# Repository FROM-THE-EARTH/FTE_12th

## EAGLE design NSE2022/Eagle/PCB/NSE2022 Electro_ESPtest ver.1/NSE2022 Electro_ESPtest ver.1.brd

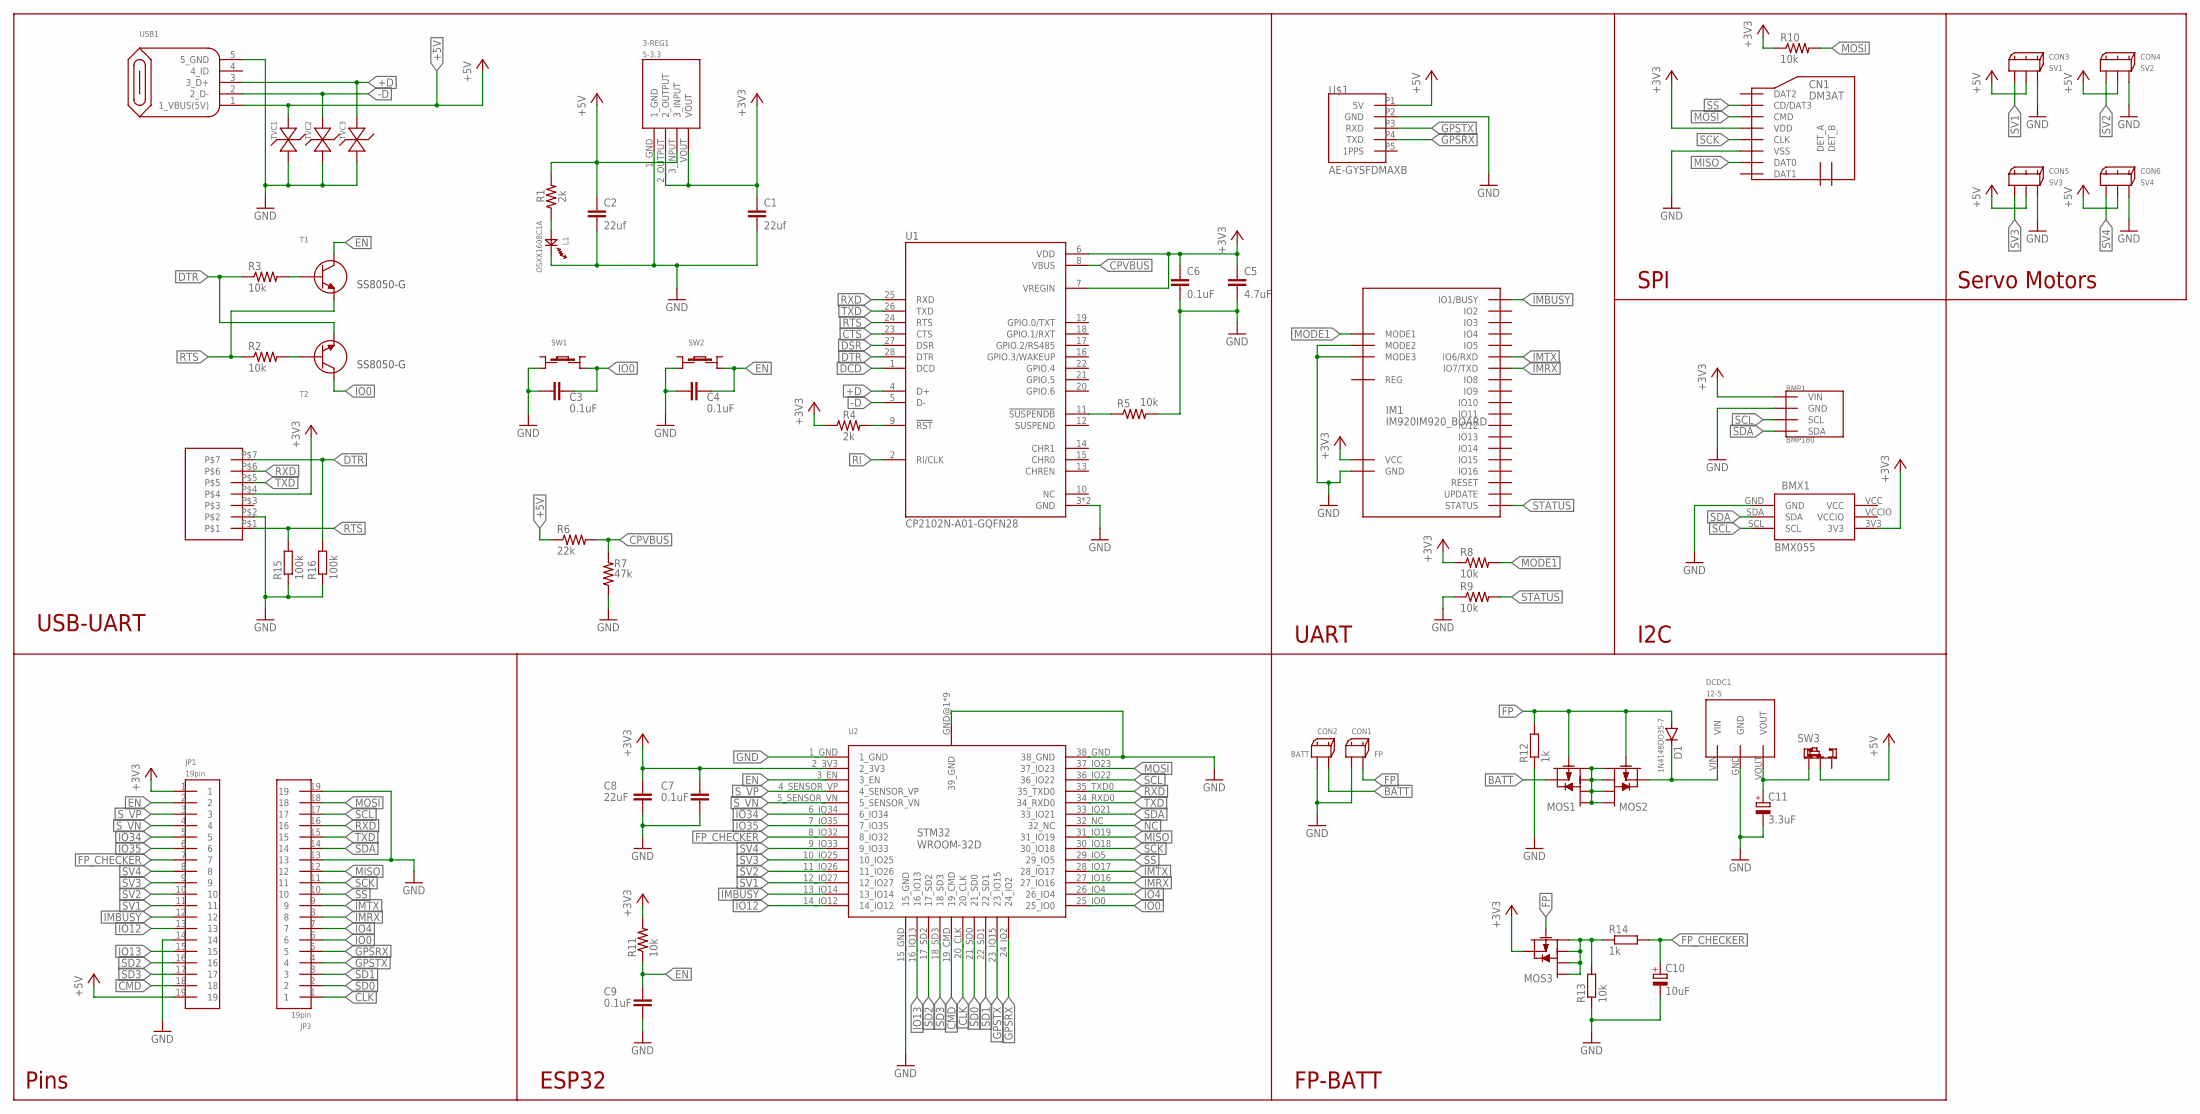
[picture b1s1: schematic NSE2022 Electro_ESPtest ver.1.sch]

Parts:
3-REG1: 5-3.3; AZ1117CH-3.3TRG1
BMP1: BMP180; GY-68
BMX1: BMX055
C1, C2: 22uf; C0603
C3, C4, C6, C7, C9: 0.1uF; C0603
C5: 4.7uF; C0402
C8: 22uF; C0603
C10: 10uF; E2,5-5
C11: 3.3uF; E2,5-5
CN1: DM3AT
CON1: FP; 2.5_MINI-SPOX_2PIN
CON2: BATT; 2.5_MINI-SPOX_2PIN
CON3: SV1; 2.5_MINI-SPOX_3PIN
CON4: SV2; 2.5_MINI-SPOX_3PIN
CON5: SV3; 2.5_MINI-SPOX_3PIN
CON6: SV4; 2.5_MINI-SPOX_3PIN
D1: 1N4148DO35-7; DO35-7
DCDC1: 12-5; 5V1A_M78AR05-1
IM1: IM920IM920_BOARD; IM920_BOARD
JP1, JP3: 19pin; 19_2.54
JP2: 7pin; 7_2.54
L1: OSXX1608C1A
MOS1, MOS2, MOS3: PCH_SSM6J808R; SSM6J808R
R1, R4: 2k; R0201
R2, R3, R5, R8, R9, R10, R11: 10k; R0201
R6: 22k; R0201
R7: 47k; R0201
R12, R14: 1k; 0207/10
R13: 10k; 0207/10
R15, R16: 100k; 0207/10
SW1, SW2: TS-06104
SW3: SRIDE_SWITCH
T1, T2: NPN_SS8050-G
TVC1, TVC2, TVC3: ESD5484FCT5G
U1: CP2102N-A01-GQFN28; QFN50P500X500X80-29N
U2: ESP32-WROOM-32D
U$1: AE-GYSFDMAXB
USB1: MICRO-B_ZX62R-B-5P

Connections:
+3V3: 3-REG1.2_OUTPUT, 3-REG1.VOUT, BMP1.P1 (VIN), BMX1.3V3, C1.1, C5.1, C6.1, C7.1, C8.1, CN1.VDD, IM1.IO23 (VCC), JP1.1, JP2.P$4, MOS3.S, R4.1, R8.1, R10.1, R11.2, U1.6 (VDD), U1.7 (VREGIN), U2.2_3V3
+5V: 3-REG1.3_INPUT, C2.1, CON3.2, CON4.2, CON5.2, CON6.2, JP1.19, R1.2, R6.1, SW3.LR, TVC1.2_AN, U$1.P1 (5V), USB1.1 (1_VBUS(5V))
+D: TVC3.2_AN, U1.4 (D+), USB1.3 (3_D+)
-D: TVC2.2_AN, U1.5 (D-), USB1.2 (2_D-)
BATT: CON2.2, MOS1.S
CLK: JP3.1, U2.20_CLK
CMD: JP1.18, U2.19_CMD
CPVBUS: R6.2, R7.2, U1.8 (VBUS)
CTS: U1.23 (CTS)
DCD: U1.1 (DCD)
DSR: U1.27 (DSR)
DTR: JP2.P$7, R3.1, R16.2, T2.2, U1.28 (DTR)
EN: C4.1, C9.1, JP1.2, R11.1, SW2.D, T1.3, U2.3_EN
FP: CON1.2, D1.A, MOS1.G, MOS2.G, MOS3.G, R12.2
FP_CHECKER: C10.+, JP1.7, R14.2, U2.8_IO32
GND: 3-REG1.1_GND, BMP1.P2 (GND), BMX1.GND, C1.2, C2.2, C3.2, C4.2, C5.2, C6.2, C7.2, C8.2, C9.2, C10.-, C11.-, CN1.VSS, CON1.1, CON2.1, CON3.3, CON4.3, CON5.3, CON6.3, DCDC1.GND, IM1.IO18 (MODE2), IM1.IO19 (MODE3), IM1.IO24 (GND), JP1.14, JP2.P$2, JP3.13, JP3.19, L1.CT, R5.2, R7.1, R9.1, R12.1, R13.1, R15.1, R16.1, SW1.B, SW2.B, TVC1.1_CT, TVC2.1_CT, TVC3.1_CT, U1.3 (GND), U1.29 (GND), U2.1_GND, U2.15_GND, U2.38_GND, U2.GND@1 (39_GND), U2.GND@2 (39_GND), U2.GND@3 (39_GND), U2.GND@4 (39_GND), U2.GND@5 (39_GND), U2.GND@6 (39_GND), U2.GND@7 (39_GND), U2.GND@8 (39_GND), U2.GND@9 (39_GND), U$1.P2 (GND), USB1.5 (5_GND)
GPSRX: JP3.5, U2.24_IO2, U$1.P4 (TXD)
GPSTX: JP3.4, U2.23_IO15, U$1.P3 (RXD)
IMBUSY: IM1.IO1 (IO1/BUSY), JP1.12, U2.13_IO14
IMRX: IM1.IO7 (IO7/TXD), JP3.8, U2.27_IO16
IMTX: IM1.IO6 (IO6/RXD), JP3.9, U2.28_IO17
IO0: C3.1, JP3.6, SW1.D, T2.3, U2.25_IO0
IO4: JP3.7, U2.26_IO4
IO12: JP1.13, U2.14_IO12
IO13: JP1.15, U2.16_IO13
IO34: JP1.5, U2.6_IO34
IO35: JP1.6, U2.7_IO35
MISO: CN1.DAT0, JP3.12, U2.31_IO19
MODE1: IM1.IO17 (MODE1), R8.2
MOSI: CN1.CMD, JP3.18, R10.2, U2.37_IO23
unnamed: L1.AN, R1.1
unnamed: R3.2, T1.1
unnamed: R2.2, T2.1
unnamed: R4.2, U1.9 (!RST)
unnamed: R5.1, U1.11 (!SUSPENDB)
unnamed: D1.C, DCDC1.VIN, MOS2.S
unnamed: MOS1.D1, MOS1.D2, MOS1.D3, MOS1.D4, MOS2.D1, MOS2.D2, MOS2.D3, MOS2.D4
unnamed: C11.+, DCDC1.VOUT, SW3.L
unnamed: MOS3.D1, MOS3.D2, MOS3.D3, MOS3.D4, R13.2, R14.1
NC: U2.32_NC
RI: U1.2 (RI/CLK)
RTS: JP2.P$1, R2.1, R15.2, T1.2, U1.24 (RTS)
RXD: JP2.P$6, JP3.16, U1.25 (RXD), U2.35_TXD0
SCK: CN1.CLK, JP3.11, U2.30_IO18
SCL: BMP1.P3 (SCL), BMX1.SCL, JP3.17, U2.36_IO22
SD0: JP3.2, U2.21_SD0
SD1: JP3.3, U2.22_SD1
SD2: JP1.16, U2.17_SD2
SD3: JP1.17, U2.18_SD3
SDA: BMP1.P4 (SDA), BMX1.SDA, JP3.14, U2.33_IO21
SS: CN1.CD/DAT3, JP3.10, U2.29_IO5
STATUS: IM1.IO21 (STATUS), R9.2
SV1: CON3.1, JP1.11, U2.12_IO27
SV2: CON4.1, JP1.10, U2.11_IO26
SV3: CON5.1, JP1.9, U2.10_IO25
SV4: CON6.1, JP1.8, U2.9_IO33
S_VN: JP1.4, U2.5_SENSOR_VN
S_VP: JP1.3, U2.4_SENSOR_VP
TXD: JP2.P$5, JP3.15, U1.26 (TXD), U2.34_RXD0
VCC: BMX1.VCC
VCCIO: BMX1.VCCIO

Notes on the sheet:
USB-UART
Pins
ESP32
UART
I2C
SPI
SS8050-G
FP-BATT
Servo Motors

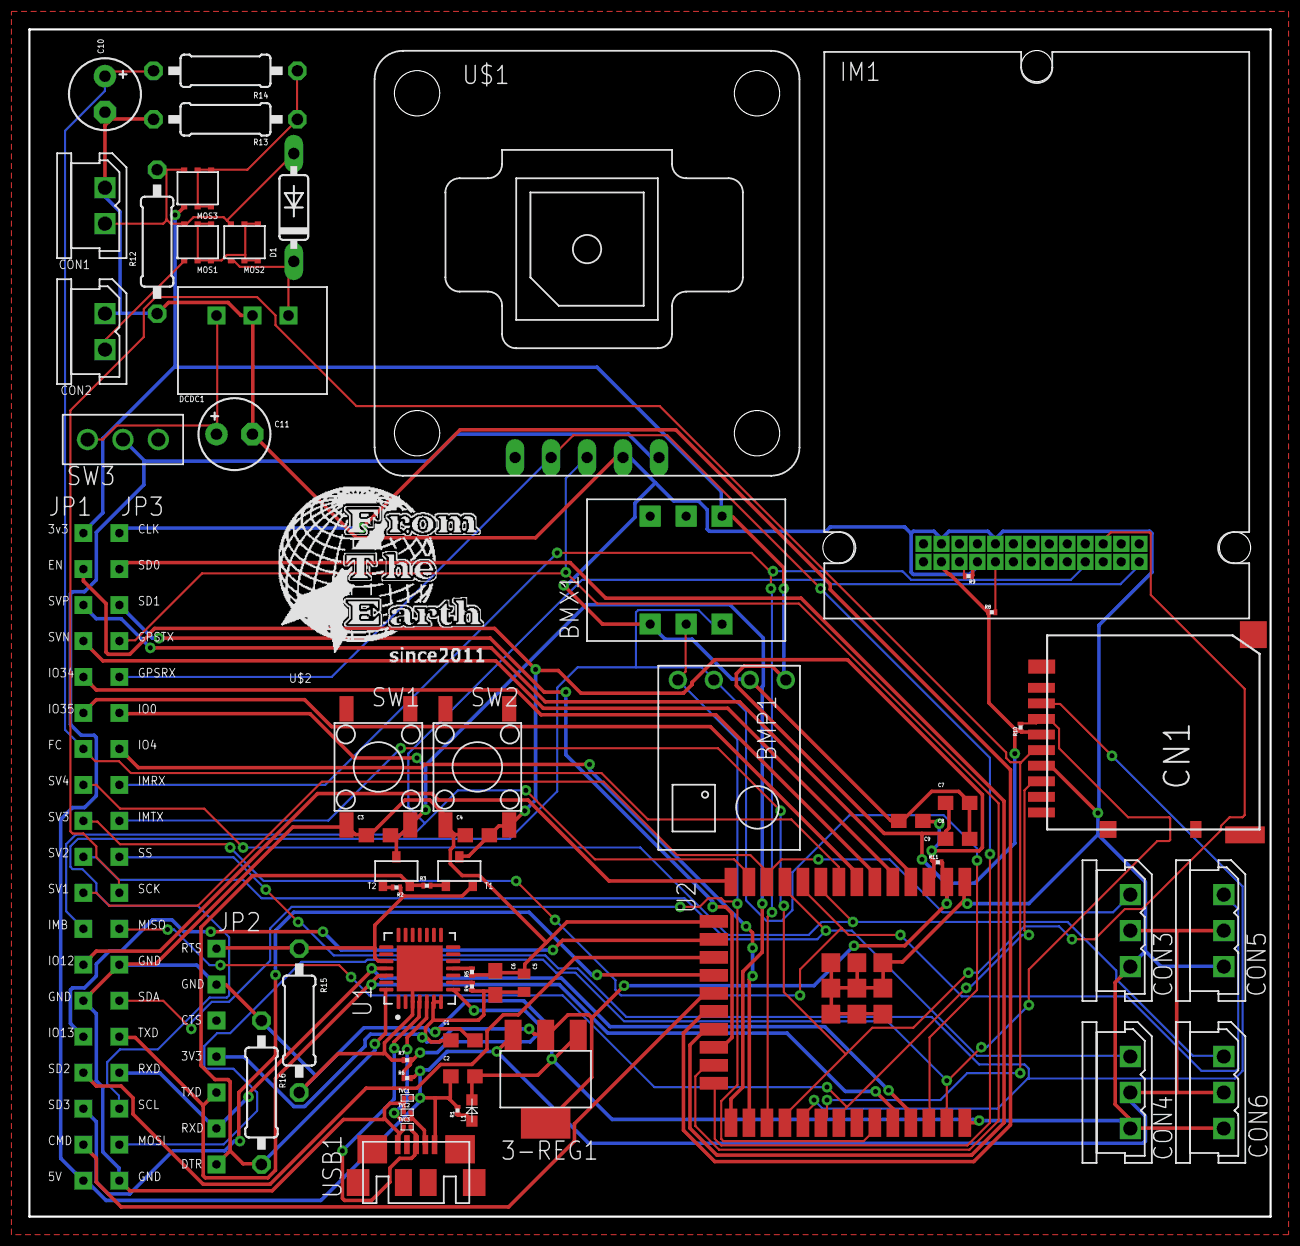
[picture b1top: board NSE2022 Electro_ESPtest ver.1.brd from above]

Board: 2 copper layers, 87.6 x 83.8 mm, 60 parts (0 on the bottom side), 54 nets.

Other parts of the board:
U$2: LOGO

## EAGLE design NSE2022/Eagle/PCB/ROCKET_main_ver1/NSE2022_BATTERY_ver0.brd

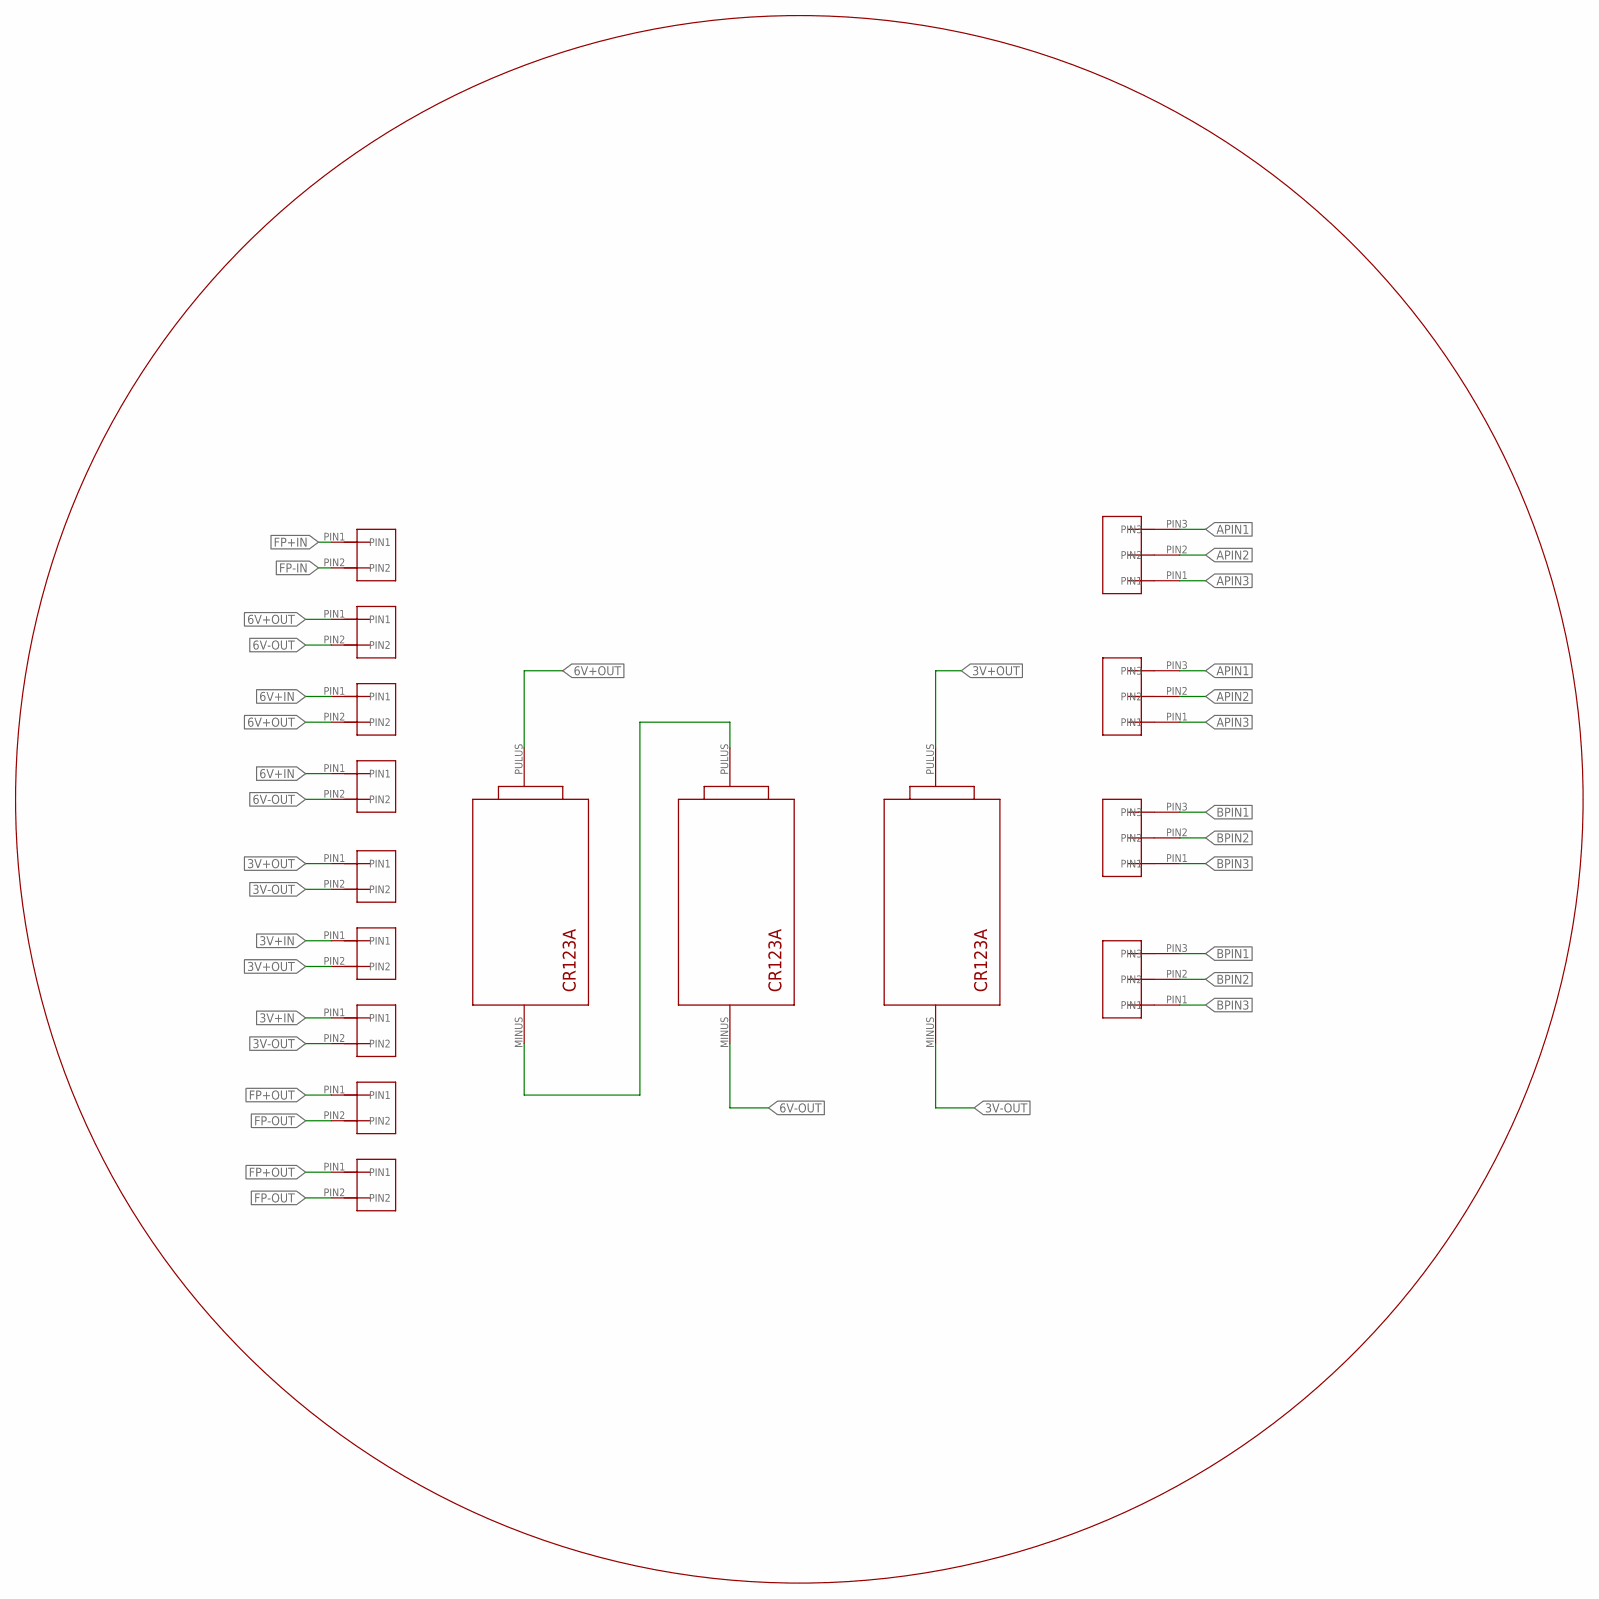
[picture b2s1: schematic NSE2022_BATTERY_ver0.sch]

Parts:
U$25, U$34, U$38: CR123A
U$41, U$45, U$56, U$57, U$58, U$65, U$66, U$67, U$68: 2PIN
U$59, U$60, U$61, U$62: 3PIN

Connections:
3V+IN: U$56.PIN1, U$65.PIN1
3V+OUT: U$38.PULUS (PULAS), U$45.PIN1, U$56.PIN2
3V-OUT: U$38.MINUS, U$45.PIN2, U$65.PIN2
6V+IN: U$67.PIN1, U$68.PIN1
6V+OUT: U$25.PULUS (PULAS), U$41.PIN1, U$67.PIN2
6V-OUT: U$34.MINUS, U$41.PIN2, U$68.PIN2
APIN1: U$59.PIN3, U$60.PIN3
APIN2: U$59.PIN2, U$60.PIN2
APIN3: U$59.PIN1, U$60.PIN1
BPIN1: U$61.PIN3, U$62.PIN3
BPIN2: U$61.PIN2, U$62.PIN2
BPIN3: U$61.PIN1, U$62.PIN1
FP+IN: U$57.PIN1
FP+OUT: U$58.PIN1, U$66.PIN1
FP-IN: U$57.PIN2
FP-OUT: U$58.PIN2, U$66.PIN2
unnamed: U$25.MINUS, U$34.PULUS (PULAS)

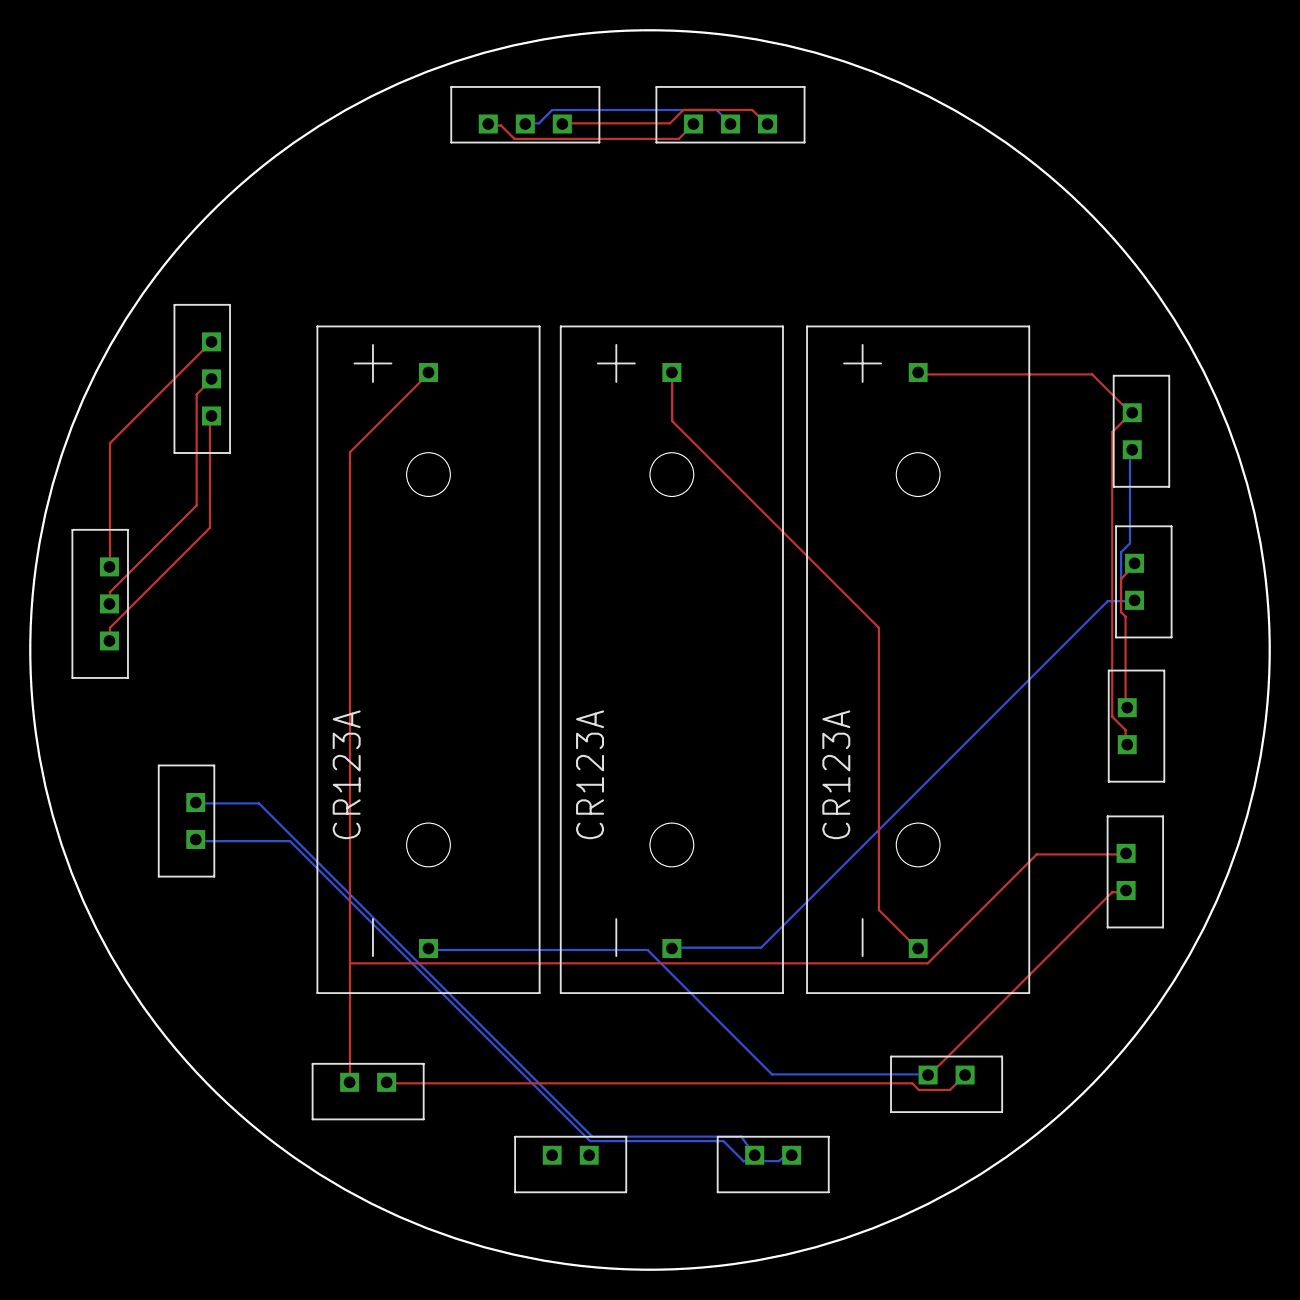
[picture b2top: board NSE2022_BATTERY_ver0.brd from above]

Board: 2 copper layers, 85.0 x 85.0 mm, 16 parts (0 on the bottom side), 15 nets.

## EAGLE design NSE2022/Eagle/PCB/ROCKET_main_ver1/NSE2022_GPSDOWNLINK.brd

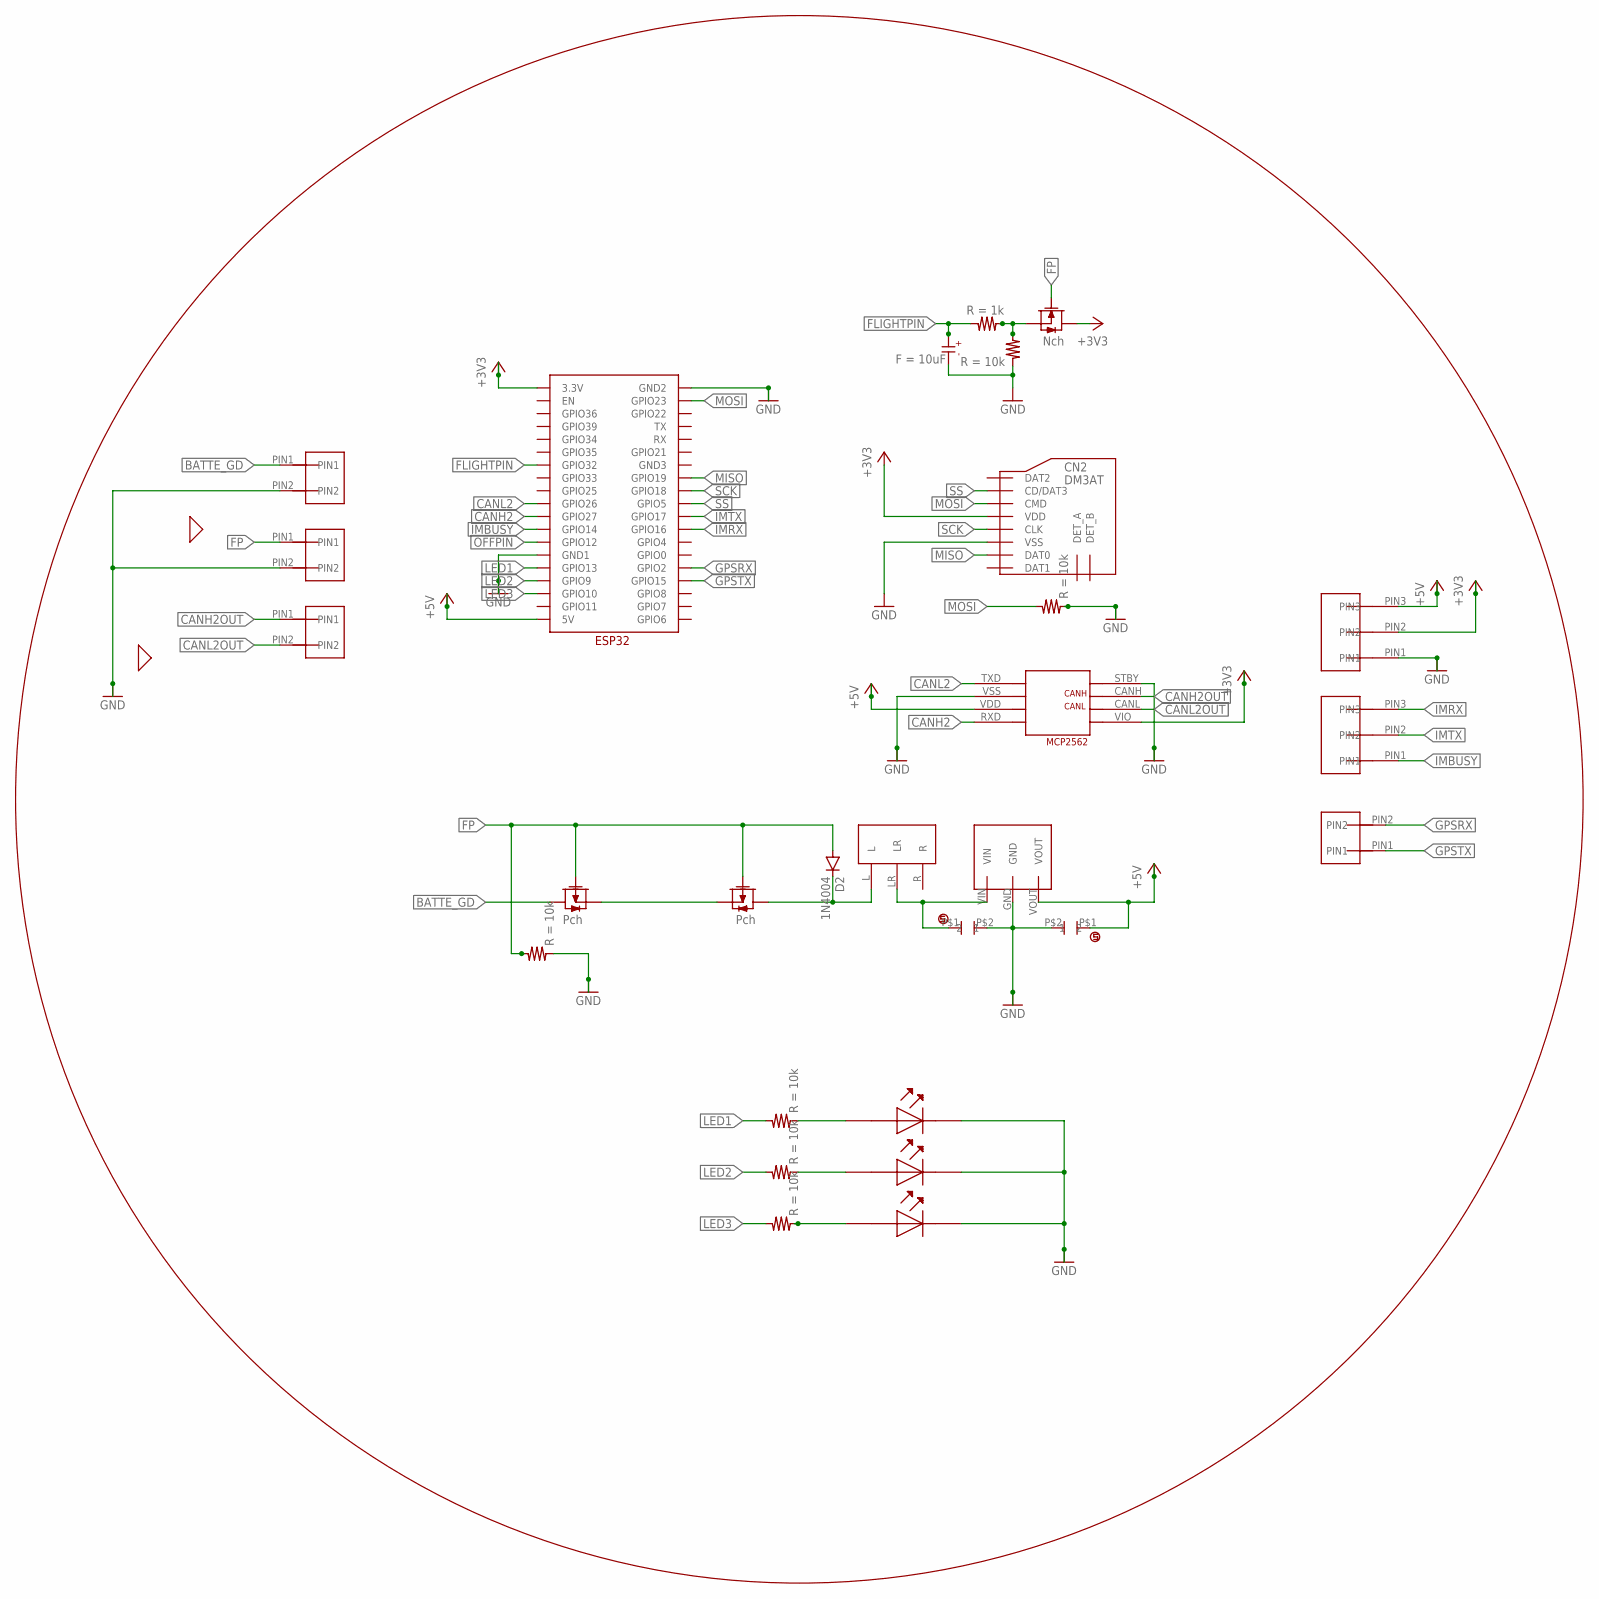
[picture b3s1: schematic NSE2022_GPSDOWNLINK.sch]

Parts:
C3: CAPACITOR-ELECTROLYTIC_1
CERAMIC_CAPACITOR1, CERAMIC_CAPACITOR2: CERAMIC_CAPACITOR
CN2: DM3AT
D2: 1N4004; DO41-10
R1, R2, R3, R4, R7, R8, R16: RESISTER; REGISTER
SRIDE_SWTCH3: SRIDE_SWITCH
U$3, U$5: 2SJ681-PCH; 2SJ681
U$6: M78AR05-1
U$7: 2SK4017-NCH; 2SK4017
U$22, U$23, U$24, U$29: 2PIN
U$26: ESP32
U$28: MCP2562
U$46, U$49: 3PIN
U$55, U$70, U$71: LED

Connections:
+3V3: CN2.VDD, U$7.DRAIN, U$26.3.3V, U$28.VIO, U$46.PIN2
+5V: CERAMIC_CAPACITOR1.P$1 (1), U$6.VOUT, U$26.5V, U$28.VDD, U$46.PIN3
BATTE_GD: U$5.DRAIN, U$22.PIN1
CANH2: U$26.GPIO27, U$28.RXD
CANH2OUT: U$24.PIN1, U$28.CANH
CANL2: U$26.GPIO26, U$28.TXD
CANL2OUT: U$24.PIN2, U$28.CANL
FLIGHTPIN: C3.KS, R8.A, U$26.GPIO32
FP: D2.A, R3.B, U$3.GATE, U$5.GATE, U$7.GATE, U$23.PIN1
GND: C3.AN, CERAMIC_CAPACITOR1.P$2 (2), CERAMIC_CAPACITOR2.P$2 (2), CN2.VSS, R3.A, R4.A, R7.A, U$6.GND, U$22.PIN2, U$23.PIN2, U$26.GND1, U$28.STBY, U$28.VSS, U$46.PIN1, U$55.PLUS (OUT), U$70.PLUS (OUT), U$71.PLUS (OUT)
GPSRX: U$26.GPIO2, U$29.PIN2
GPSTX: U$26.GPIO15, U$29.PIN1
IMBUSY: U$26.GPIO14, U$49.PIN1
IMRX: U$26.GPIO16, U$49.PIN3
IMTX: U$26.GPIO17, U$49.PIN2
LED1: R1.B, U$26.GPIO13
LED2: R2.B, U$26.GPIO9
LED3: R16.B, U$26.GPIO10
MISO: CN2.DAT0, U$26.GPIO19
MOSI: CN2.CMD, R4.B, U$26.GPIO23
unnamed: U$3.SOURCE, U$5.SOURCE
unnamed: CERAMIC_CAPACITOR2.P$1 (1), SRIDE_SWTCH3.LR, U$6.VIN
unnamed: R7.B, R8.B, U$7.SOURCE
unnamed: D2.C, SRIDE_SWTCH3.L, U$3.DRAIN
unnamed: R1.A, U$55.MINUS (IN)
unnamed: R2.A, U$70.MINUS (IN)
unnamed: R16.A, U$71.MINUS (IN)
OFFPIN: U$26.GPIO12
SCK: CN2.CLK, U$26.GPIO18
SS: CN2.CD/DAT3, U$26.GPIO5

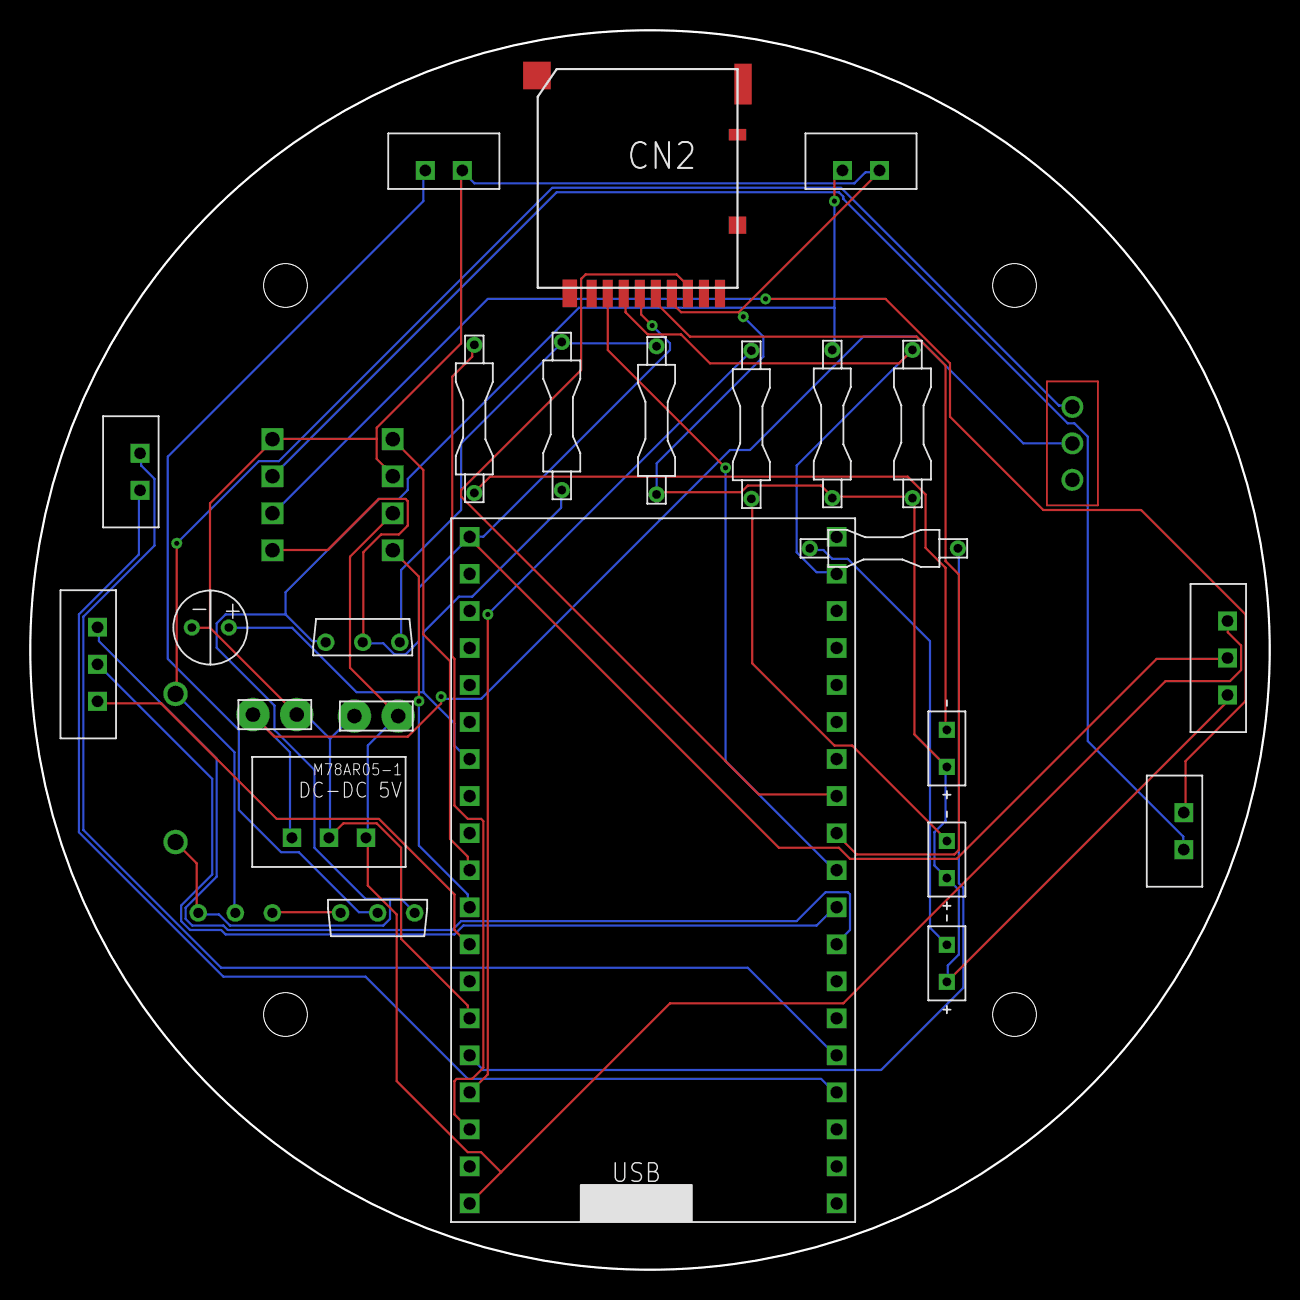
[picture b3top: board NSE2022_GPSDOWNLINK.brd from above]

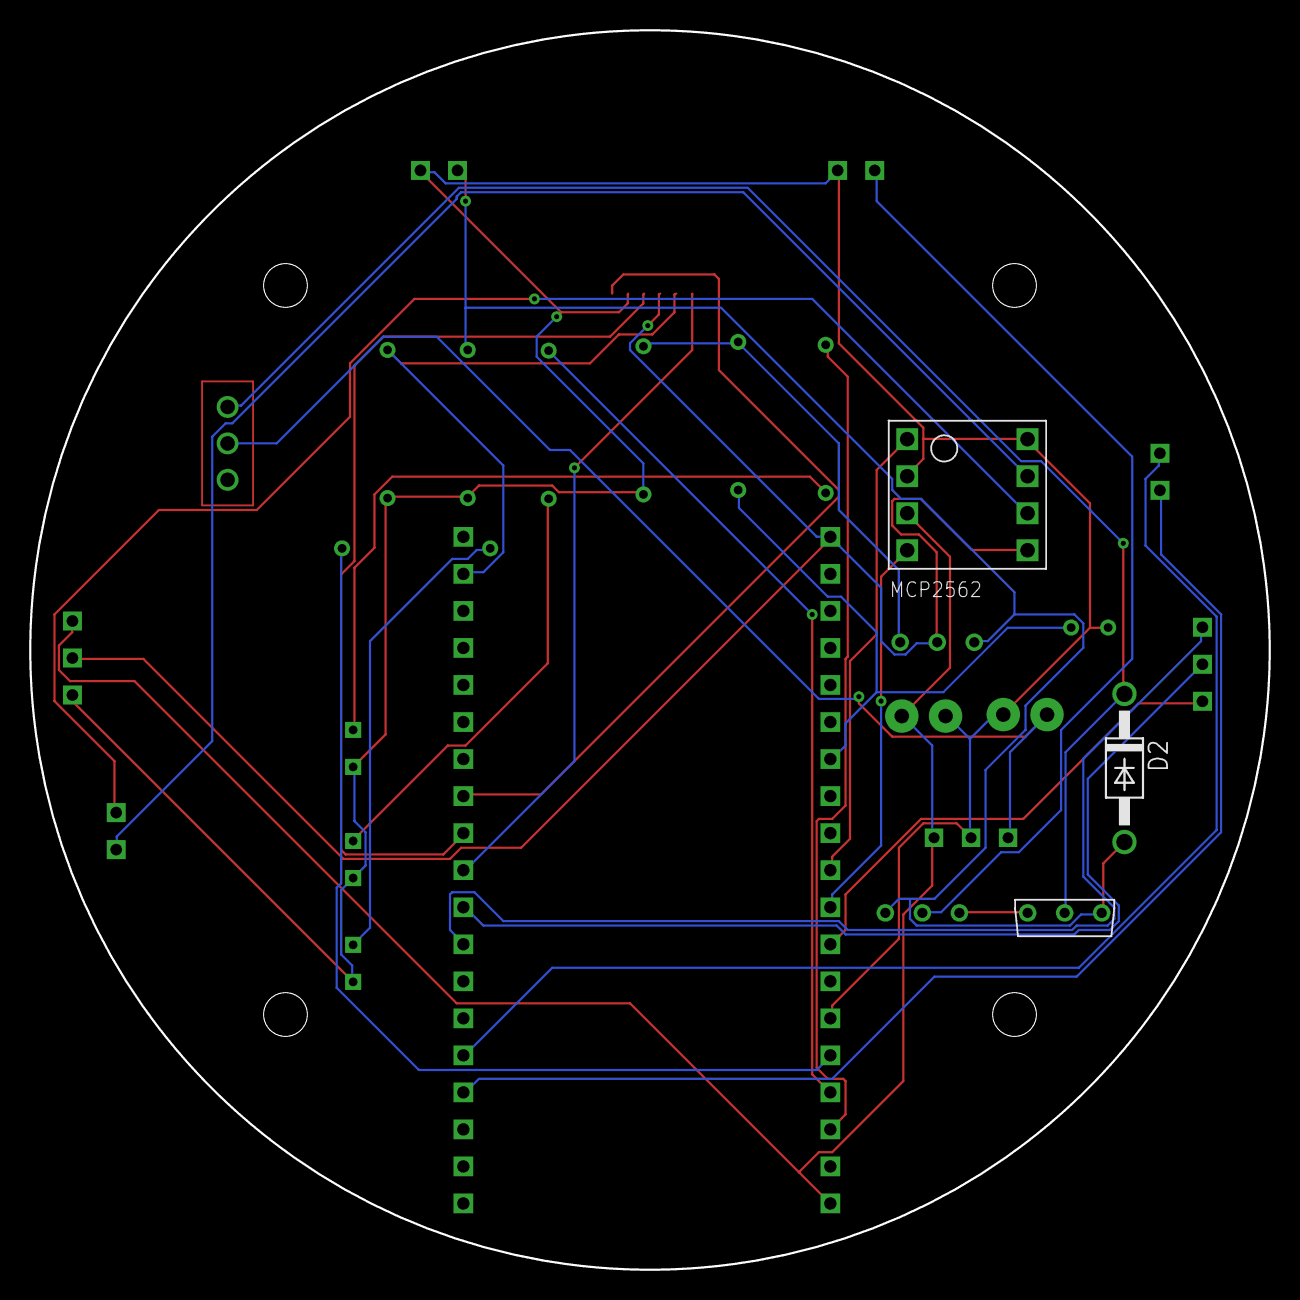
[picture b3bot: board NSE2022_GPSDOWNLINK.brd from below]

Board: 2 copper layers, 85.0 x 85.0 mm, 28 parts (3 on the bottom side), 29 nets.

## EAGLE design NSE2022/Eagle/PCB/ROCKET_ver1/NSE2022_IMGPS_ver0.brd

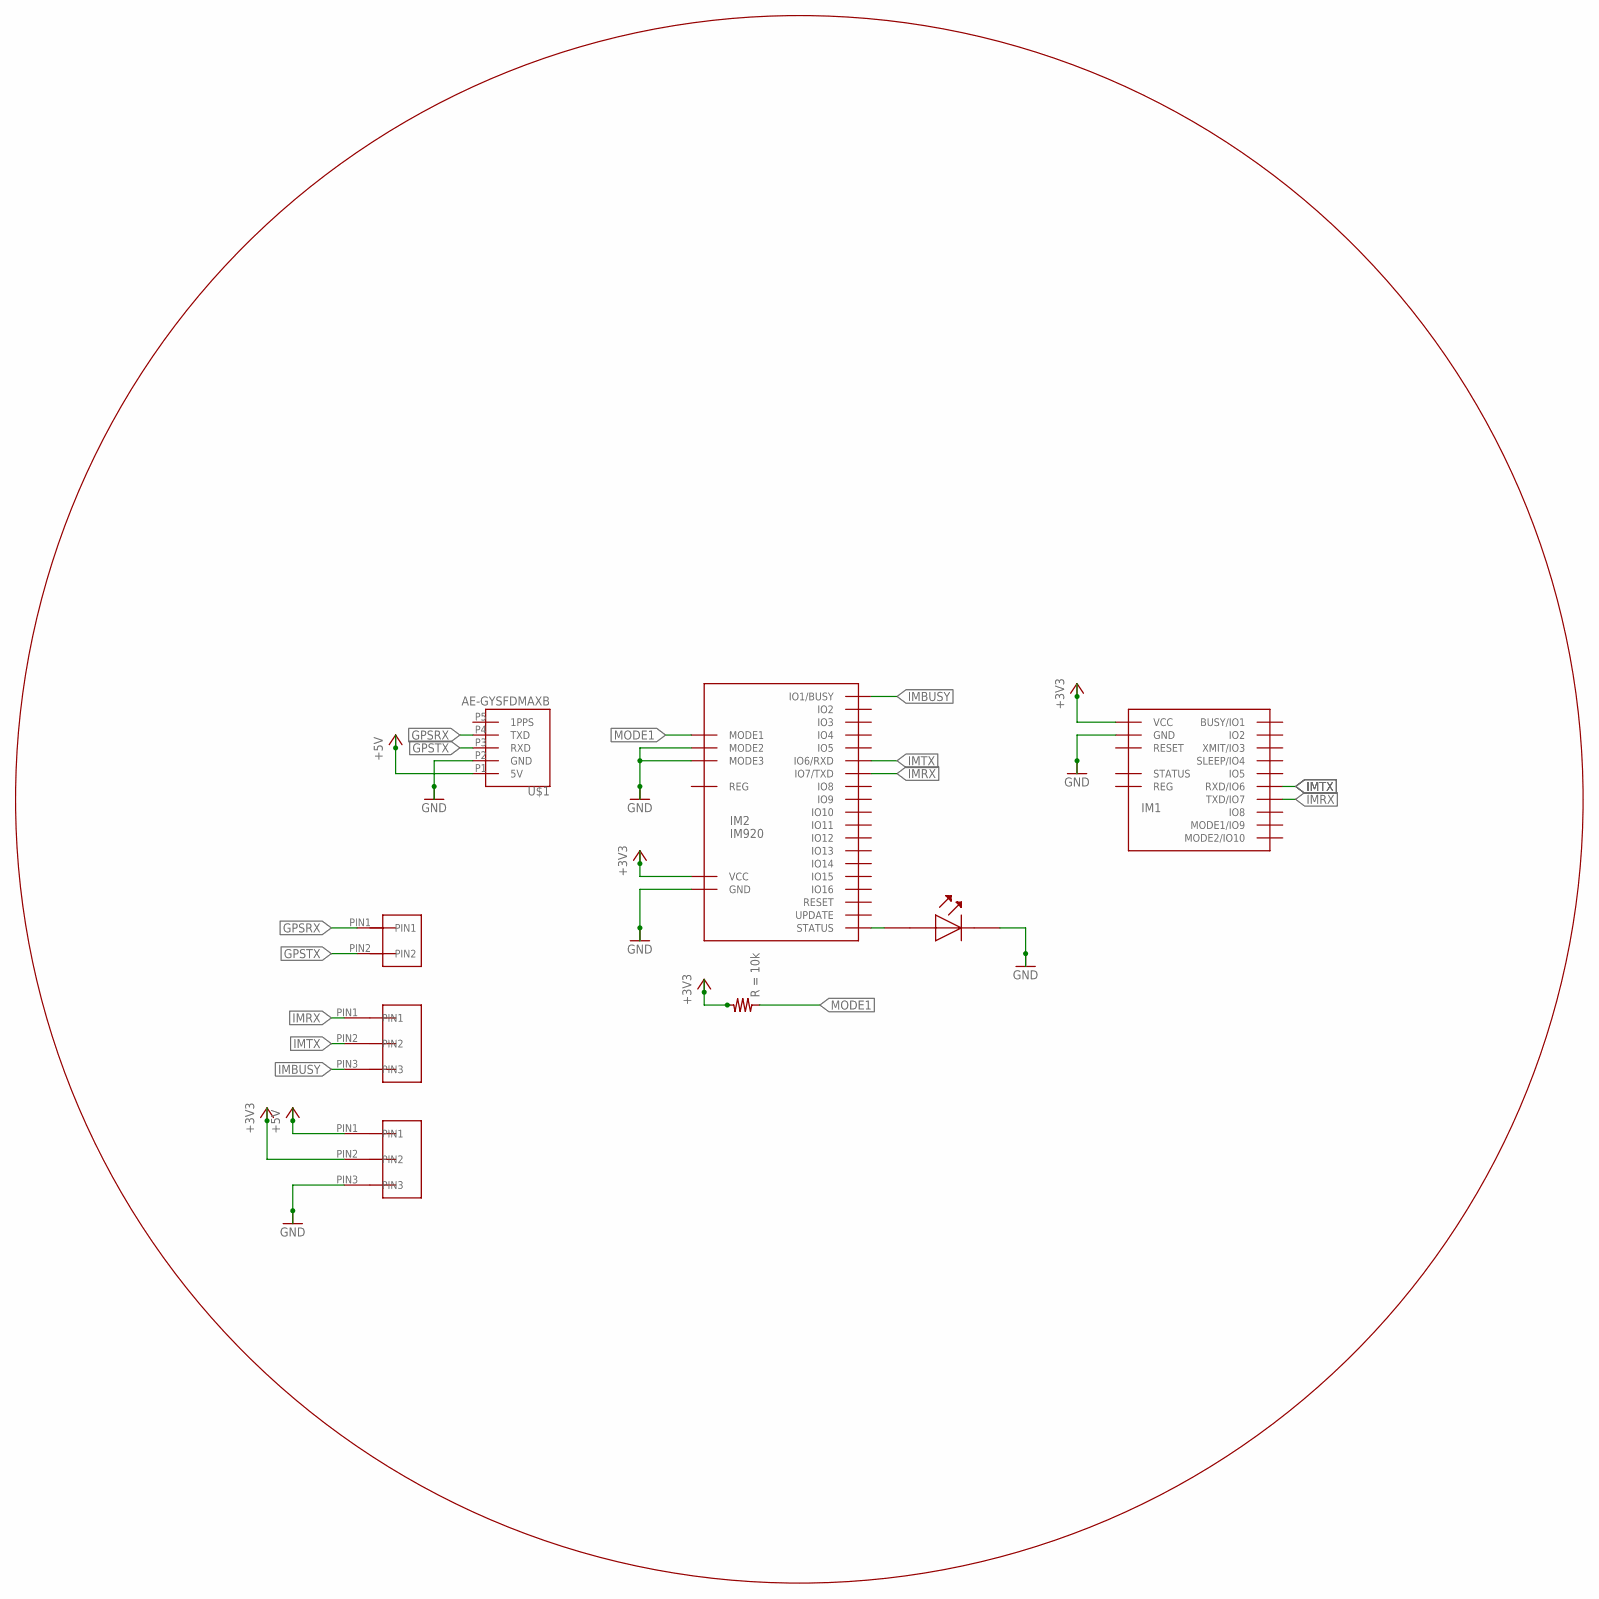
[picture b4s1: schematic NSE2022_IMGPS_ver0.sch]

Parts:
IM1: IM920C
IM2: IM920
R4: RESISTER; REGISTER
U$1: AE-GYSFDMAXB
U$33: 2PIN
U$47, U$48: 3PIN
U$54: LED

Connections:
+3V3: IM1.$P17 (VCC), IM2.IO23 (VCC), R4.B, U$48.PIN2
+5V: U$1.P1 (5V), U$48.PIN1
GND: IM1.$P18 (GND), IM2.IO18 (MODE2), IM2.IO19 (MODE3), IM2.IO24 (GND), U$1.P2 (GND), U$48.PIN3, U$54.PLUS (OUT)
GPSRX: U$1.P4 (TXD), U$33.PIN1
GPSTX: U$1.P3 (RXD), U$33.PIN2
IMBUSY: IM2.IO1 (IO1/BUSY), U$47.PIN3
IMRX: IM1.$P7 (TXD/IO7), IM2.IO7 (IO7/TXD), U$47.PIN1
IMTX: IM1.$P6 (RXD/IO6), IM2.IO6 (IO6/RXD), U$47.PIN2
MODE1: IM2.IO17 (MODE1), R4.A
unnamed: IM2.IO21 (STATUS), U$54.MINUS (IN)
